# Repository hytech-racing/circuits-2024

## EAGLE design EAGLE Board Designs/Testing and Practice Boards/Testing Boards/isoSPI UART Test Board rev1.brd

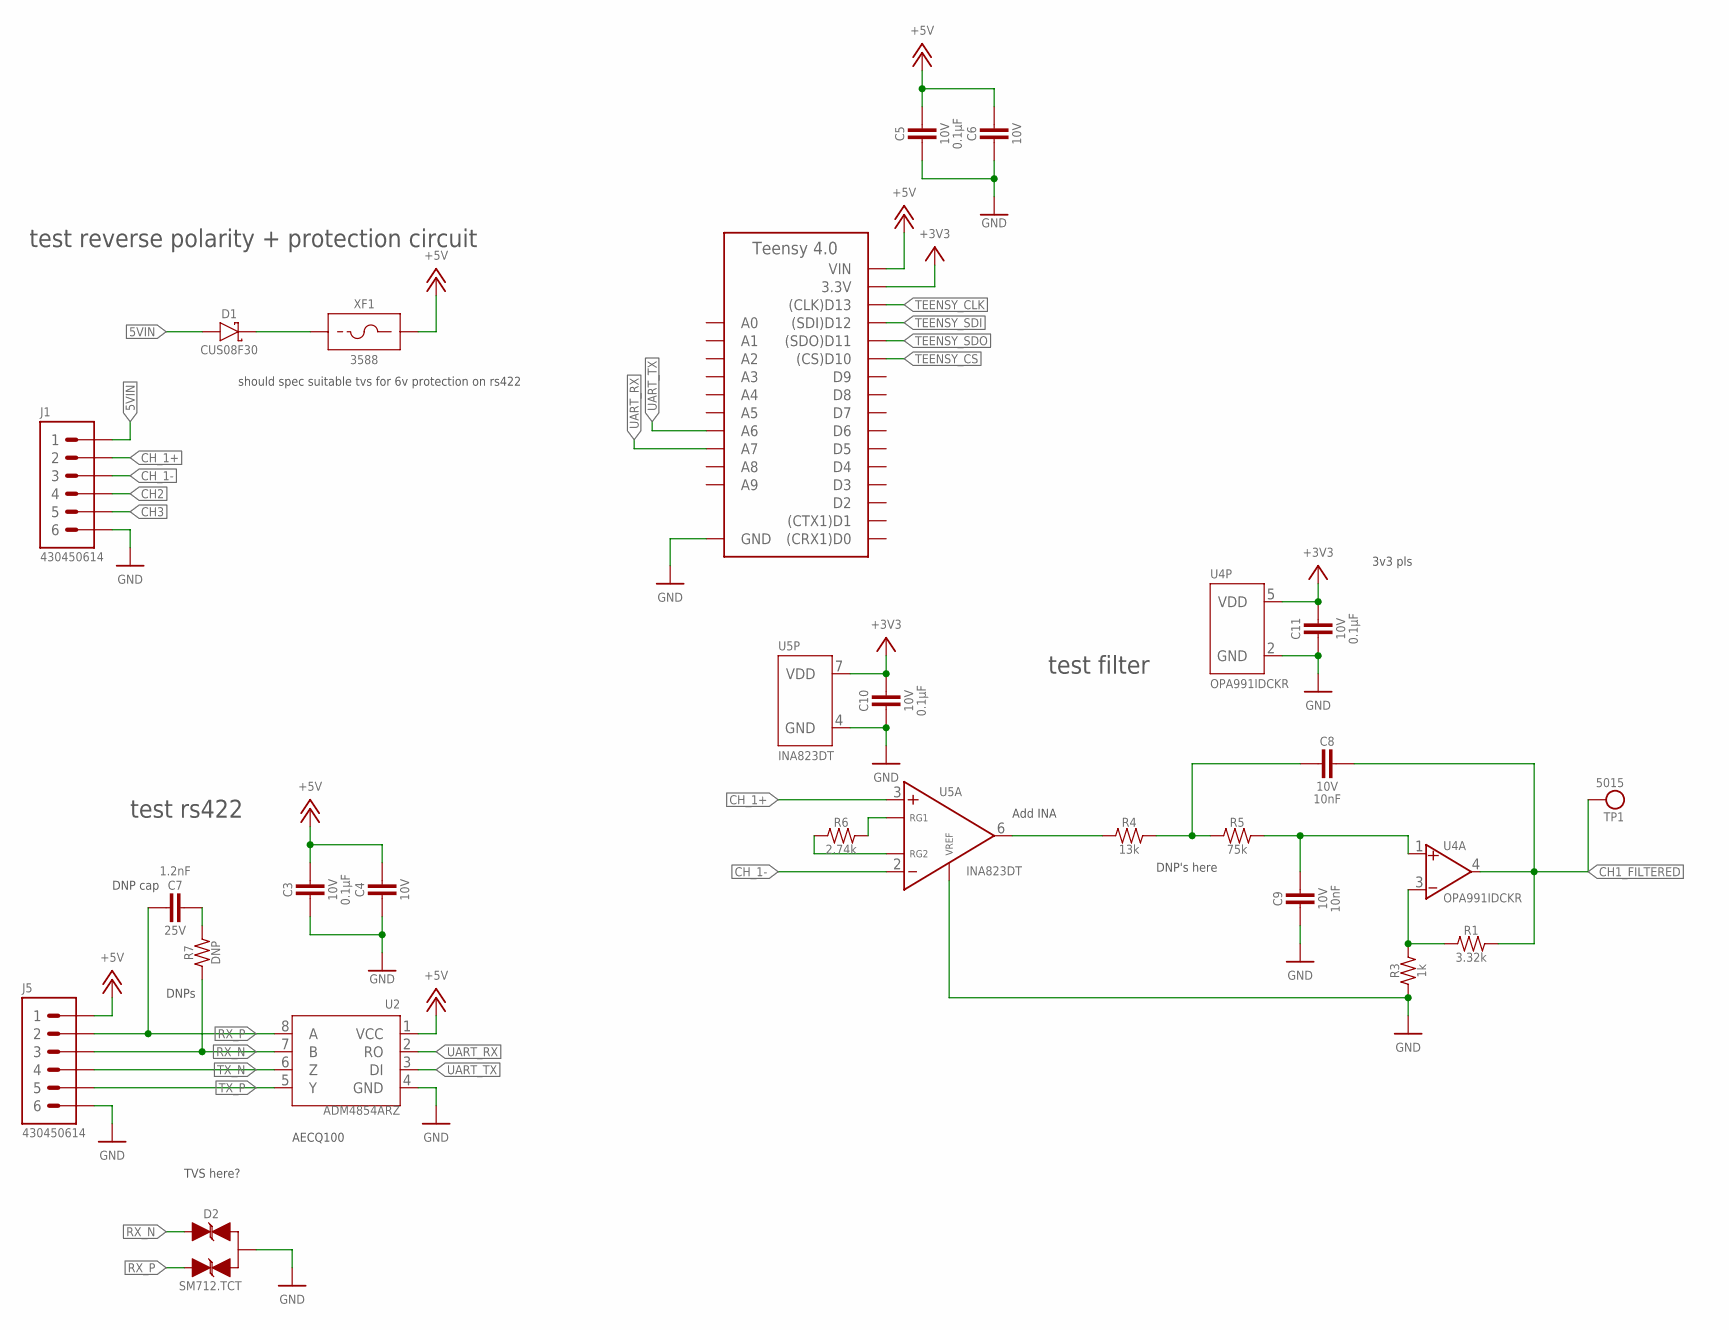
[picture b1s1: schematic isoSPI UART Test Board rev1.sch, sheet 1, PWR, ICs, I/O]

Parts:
A1: TEENSY_4.0TH; TEENSY_SHORT
C3, C5, C10, C11: CAPACITOR_0603_10V_0.1UF; 0603-CAP
C4, C6: CAPACITOR_0603_10V_1UF; 0603-CAP
C7: CAPACITOR_0603_25V_1.2NF; 0603-CAP
C8, C9: CAPACITOR_0603_10V_10NF; 0603-CAP
D1: SCHOTTKY_SOD323_30V; SOD-323
D2: TVS_BIDIRECTIONAL_DUALRS422; SOT-23
J1, J5: CONNECTOR-6_μF_T_V_BLACK; MOLEX_MICROFIT_PTH_VERTICAL_06_DUAL
R1: RESISTOR_0603_3.32K; 0603-RES
R3: RESISTOR_0603_1K; 0603-RES
R4: RESISTOR_0603_13K; 0603-RES
R5: RESISTOR_0603_75K; 0603-RES
R6: RESISTOR_0603_2.74K; 0603-RES
R7: RESISTOR_0603_DNP; 0603-RES
TP1: TEST_POINT; 5015
U2: ADM4854ARZ; SOIC-08(NARROW,0.15")
U4: OPAMP_1_CHANNEL_OPA991; SC-70-5
U5: INA823DT; SOIC-08(NARROW,0.15")
XF1: FUSE_HOLDER_MINIBLADESMD; 3588

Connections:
5VIN: D1.A, J1.1
+3V3: A1.3.3V, C10.1, C11.1, U4.5 (VDD), U5.7 (VDD); also elsewhere on the board
+5V: A1.VIN, C3.1, C4.1, C5.1, C6.1, J5.1, U2.1 (VCC), XF1.3 (2), XF1.4 (2)
CH1: R4.1, U5.6 (VOUT)
CH1_FILTERED: C8.1, R1.2, TP1.1, U4.4 (VOUT); also elsewhere on the board
CH2: J1.4; also elsewhere on the board
CH3: J1.5; also elsewhere on the board
CH_1+: J1.2, U5.3 (VIN+)
CH_1-: J1.3, U5.2 (VIN-)
GND: A1.AGND/GND (GND), A1.GND, C3.2, C4.2, C5.2, C6.2, C9.2, C10.2, C11.2, D2.3 (A), J1.6, J5.6, R3.1, U2.4 (GND), U4.2 (GND), U5.4 (GND), U5.5 (VREF); also elsewhere on the board
unnamed: C7.1, R7.2
unnamed: D1.C, XF1.1, XF1.2 (1)
unnamed: R1.1, R3.2, U4.3 (VIN-)
unnamed: R6.2, U5.1 (RG1)
unnamed: R6.1, U5.8 (RG2)
unnamed: C8.2, R4.2, R5.1
unnamed: C9.1, R5.2, U4.1 (VIN+)
RX_N: D2.1 (C1), J5.3, R7.1, U2.7 (B)
RX_P: C7.2, D2.2 (C2), J5.2, U2.8 (A)
TEENSY_CLK: A1.D13 ((CLK)D13); also elsewhere on the board
TEENSY_CS: A1.D10 ((CS)D10); also elsewhere on the board
TEENSY_SDI: A1.D12 ((SDI)D12); also elsewhere on the board
TEENSY_SDO: A1.D11 ((SDO)D11); also elsewhere on the board
TX_N: J5.4, U2.6 (Z)
TX_P: J5.5, U2.5 (Y)
UART_RX: A1.D21 (A7), U2.2 (RO)
UART_TX: A1.D20 (A6), U2.3 (DI)

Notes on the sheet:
DNP cap
test reverse polarity + protection circuit
test rs422
test filter
DNPs
should spec suitable tvs for 6v protection on rs422
TVS here?
DNP's here
Add INA
3v3 pls
AECQ100

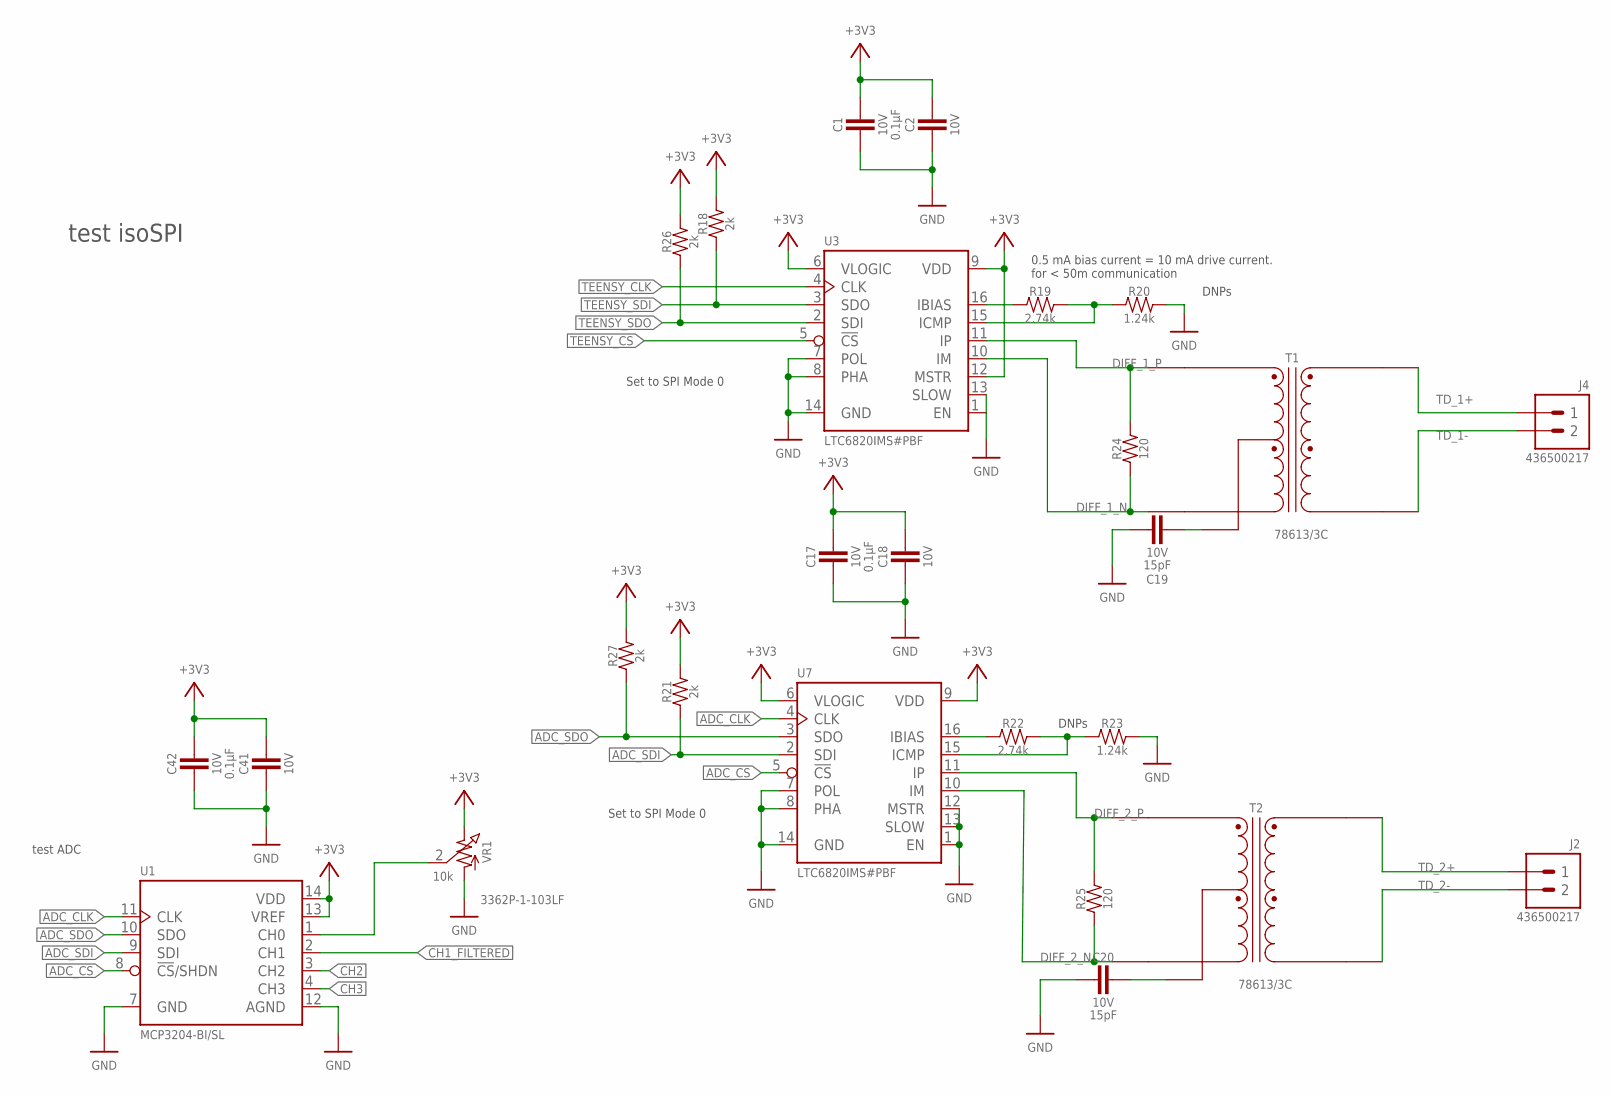
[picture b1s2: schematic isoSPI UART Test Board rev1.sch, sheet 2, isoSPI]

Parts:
C1, C17, C42: CAPACITOR_0603_10V_0.1UF; 0603-CAP
C2, C18, C41: CAPACITOR_0603_10V_1UF; 0603-CAP
C19, C20: CAPACITOR_0603_10V_15PF; 0603-CAP
J2, J4: CONNECTOR-2_MF_T_V_; MOLEX_MICROFIT_PTH_VERTICAL_02_SINGLE
R18, R21, R26, R27: RESISTOR_0603_2K; 0603-RES
R19, R22: RESISTOR_0603_2.74K; 0603-RES
R20, R23: RESISTOR_0603_1.24K; 0603-RES
R24, R25: RESISTOR_0603_120; 0603-RES
T1, T2: 78613/3C
U1: MCP3204; SOIC-14
U3, U7: LTC6820; MSOP-16
VR1: RESISTOR_TRIMPOT_10K_3362P; 3362P

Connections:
+3V3: C1.1, C2.1, C17.1, C18.1, C41.1, C42.1, R18.2, R21.2, R26.2, R27.2, U1.13 (VREF), U1.14 (VDD), U3.6 (VLOGIC), U3.9 (VDD), U3.12 (MSTR), U7.6 (VLOGIC), U7.9 (VDD), VR1.3 (2); also elsewhere on the board
ADC_CLK: U1.11 (CLK), U7.4 (CLK)
ADC_CS: U1.8 (!CS!/SHDN), U7.5 (!CS)
ADC_SDI: R21.1, U1.9 (SDI), U7.2 (SDI)
ADC_SDO: R27.1, U1.10 (SDO), U7.3 (SDO)
CH1_FILTERED: U1.2 (CH1); also elsewhere on the board
CH2: U1.3 (CH2); also elsewhere on the board
CH3: U1.4 (CH3); also elsewhere on the board
DIFF_1_N: R24.1, T1.3 (PRI_2), U3.10 (IM)
DIFF_1_P: R24.2, T1.1 (PRI_1), U3.11 (IP)
DIFF_2_N: R25.1, T2.3 (PRI_2), U7.10 (IM)
DIFF_2_P: R25.2, T2.1 (PRI_1), U7.11 (IP)
GND: C1.2, C2.2, C17.2, C18.2, C19.2, C20.2, C41.2, C42.2, R20.2, R23.2, U1.7 (GND), U1.12 (AGND), U3.1 (EN), U3.7 (POL), U3.8 (PHA), U3.13 (SLOW), U3.14 (GND), U7.1 (EN), U7.7 (POL), U7.8 (PHA), U7.12 (MSTR), U7.13 (SLOW), U7.14 (GND), VR1.1; also elsewhere on the board
unnamed: U1.1 (CH0), VR1.2 (3)
unnamed: R19.1, U3.16 (IBIAS)
unnamed: R19.2, R20.1, U3.15 (ICMP)
unnamed: R22.1, U7.16 (IBIAS)
unnamed: R22.2, R23.1, U7.15 (ICMP)
unnamed: C19.1, T1.2 (PRI_CENTER_TAP)
unnamed: C20.1, T2.2 (PRI_CENTER_TAP)
TD_1+: J4.1, T1.6 (SEC_2)
TD_1-: J4.2, T1.4 (SEC_1)
TD_2+: J2.1, T2.6 (SEC_2)
TD_2-: J2.2, T2.4 (SEC_1)
TEENSY_CLK: U3.4 (CLK); also elsewhere on the board
TEENSY_CS: U3.5 (!CS); also elsewhere on the board
TEENSY_SDI: R18.1, U3.3 (SDO); also elsewhere on the board
TEENSY_SDO: R26.1, U3.2 (SDI); also elsewhere on the board

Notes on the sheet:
0.5 mA bias current = 10 mA drive current. for < 50m communication
DNPs
test ADC
test isoSPI
Set to SPI Mode 0

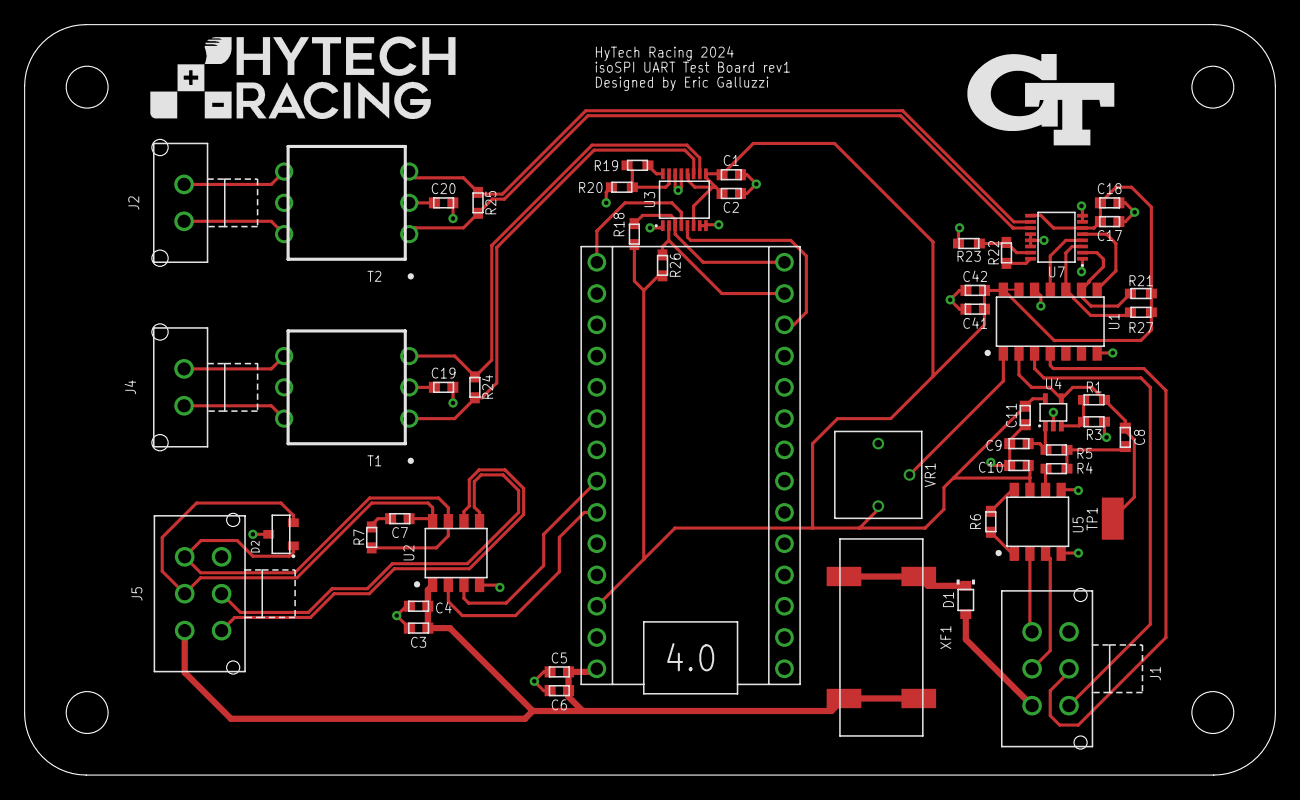
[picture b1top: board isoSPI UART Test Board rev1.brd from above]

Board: 2 copper layers, 101.6 x 61.0 mm, 57 parts (1 on the bottom side), 46 nets.

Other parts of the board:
U$1, U$2, U$3, U$4: MOUNTING_M3
U$5: LOGO_HYTECH_MEDIUM
U$6: LOGO_GT_MEDIUM

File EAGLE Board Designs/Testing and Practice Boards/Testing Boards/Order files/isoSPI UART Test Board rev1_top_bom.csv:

Comment,Designator,Footprint,LCSC Part #
ADM4854ARZ,U2,SOIC-08(NARROW 0.15"),
CAPACITOR_0603_10V_0.1UF,C1 C3 C5 C10 C11 C17 C42,0603-CAP,
CAPACITOR_0603_10V_1UF,C2 C4 C6 C18 C41,0603-CAP,
CAPACITOR_0603_10V_10NF,C8 C9,0603-CAP,
CAPACITOR_0603_10V_15PF,C19 C20,0603-CAP,
CAPACITOR_0603_25V_1.2NF,C7,0603-CAP,
FUSE_HOLDER_MINIBLADESMD,XF1,3588,
INA823DT,U5,SOIC-08(NARROW 0.15"),
LTC6820,U3 U7,MSOP-16,
MCP3204,U1,SOIC-14,
OPAMP_1_CHANNEL_OPA991,U4,SC-70-5,
RESISTOR_0603_1.24K,R20 R23,0603-RES,
RESISTOR_0603_1K,R3,0603-RES,
RESISTOR_0603_2.74K,R6 R19 R22,0603-RES,
RESISTOR_0603_2K,R18 R21 R26 R27,0603-RES,
RESISTOR_0603_3.32K,R1,0603-RES,
RESISTOR_0603_13K,R4,0603-RES,
RESISTOR_0603_75K,R5,0603-RES,
RESISTOR_0603_120,R24 R25,0603-RES,
RESISTOR_0603_DNP,R7,0603-RES,
RESISTOR_1206_HV46.4K,R2,1206-RES,
SCHOTTKY_SOD323_30V,D1,SOD-323,
TEST_POINT,TP1,5015,
TVS_BIDIRECTIONAL_DUALRS422,D2,SOT-23,

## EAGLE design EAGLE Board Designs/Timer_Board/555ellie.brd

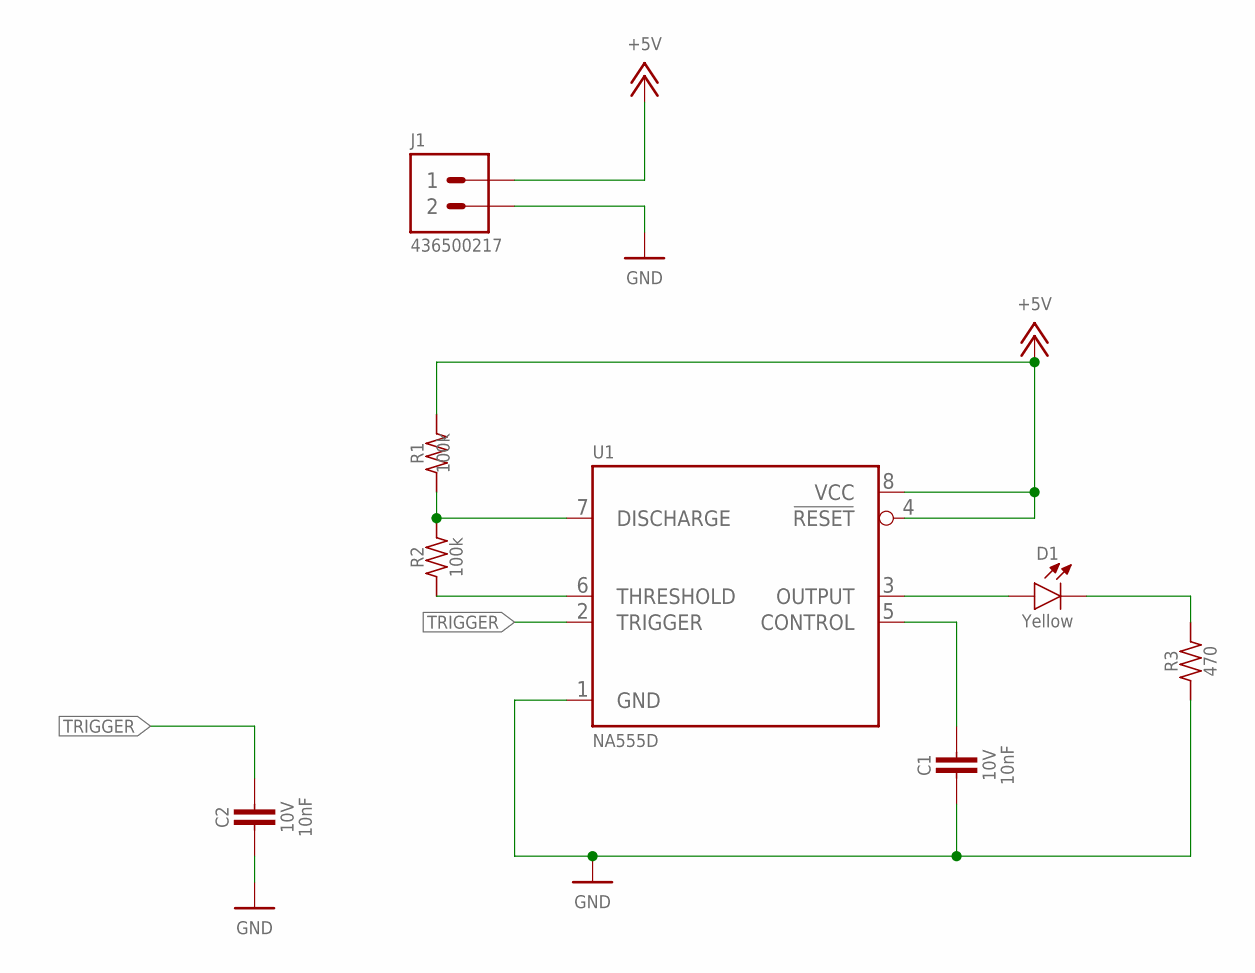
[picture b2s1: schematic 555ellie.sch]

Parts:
C1, C2: CAPACITOR_0603_10V_10NF; 0603-CAP
D1: LED_0603_YELLOW; 0603-LED
J1: CONNECTOR-2_μF_T_V_BLACK; MOLEX_MICROFIT_PTH_VERTICAL_02_DUAL
R1, R2: RESISTOR_0603_100K; 0603-RES
R3: RESISTOR_0603_470; 0603-RES
U1: NA555; SOIC-08(NARROW,0.15")

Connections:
+5V: J1.1, R1.2, U1.4 (!RESET), U1.8 (VCC)
GND: C2.2, J1.2
unnamed: R2.1, U1.6 (THRESHOLD)
unnamed: R1.1, R2.2, U1.7 (DISCHARGE)
unnamed: D1.2 (A), U1.3 (OUTPUT)
unnamed: D1.1 (C), R3.2
unnamed: C1.2, R3.1, U1.1 (GND)
unnamed: C1.1, U1.5 (CONTROL)
TRIGGER: C2.1, U1.2 (TRIGGER)

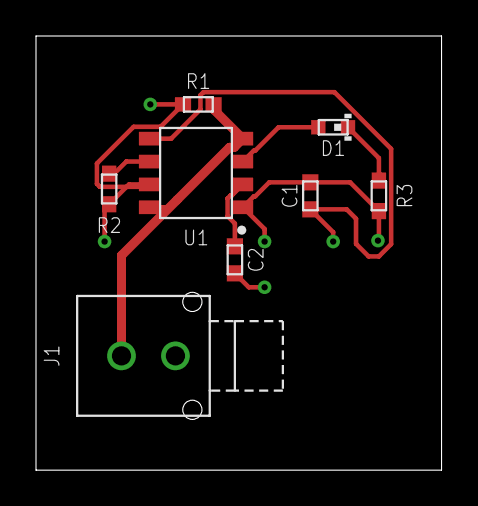
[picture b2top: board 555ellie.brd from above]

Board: 2 copper layers, 22.5 x 24.1 mm, 8 parts (0 on the bottom side), 9 nets.

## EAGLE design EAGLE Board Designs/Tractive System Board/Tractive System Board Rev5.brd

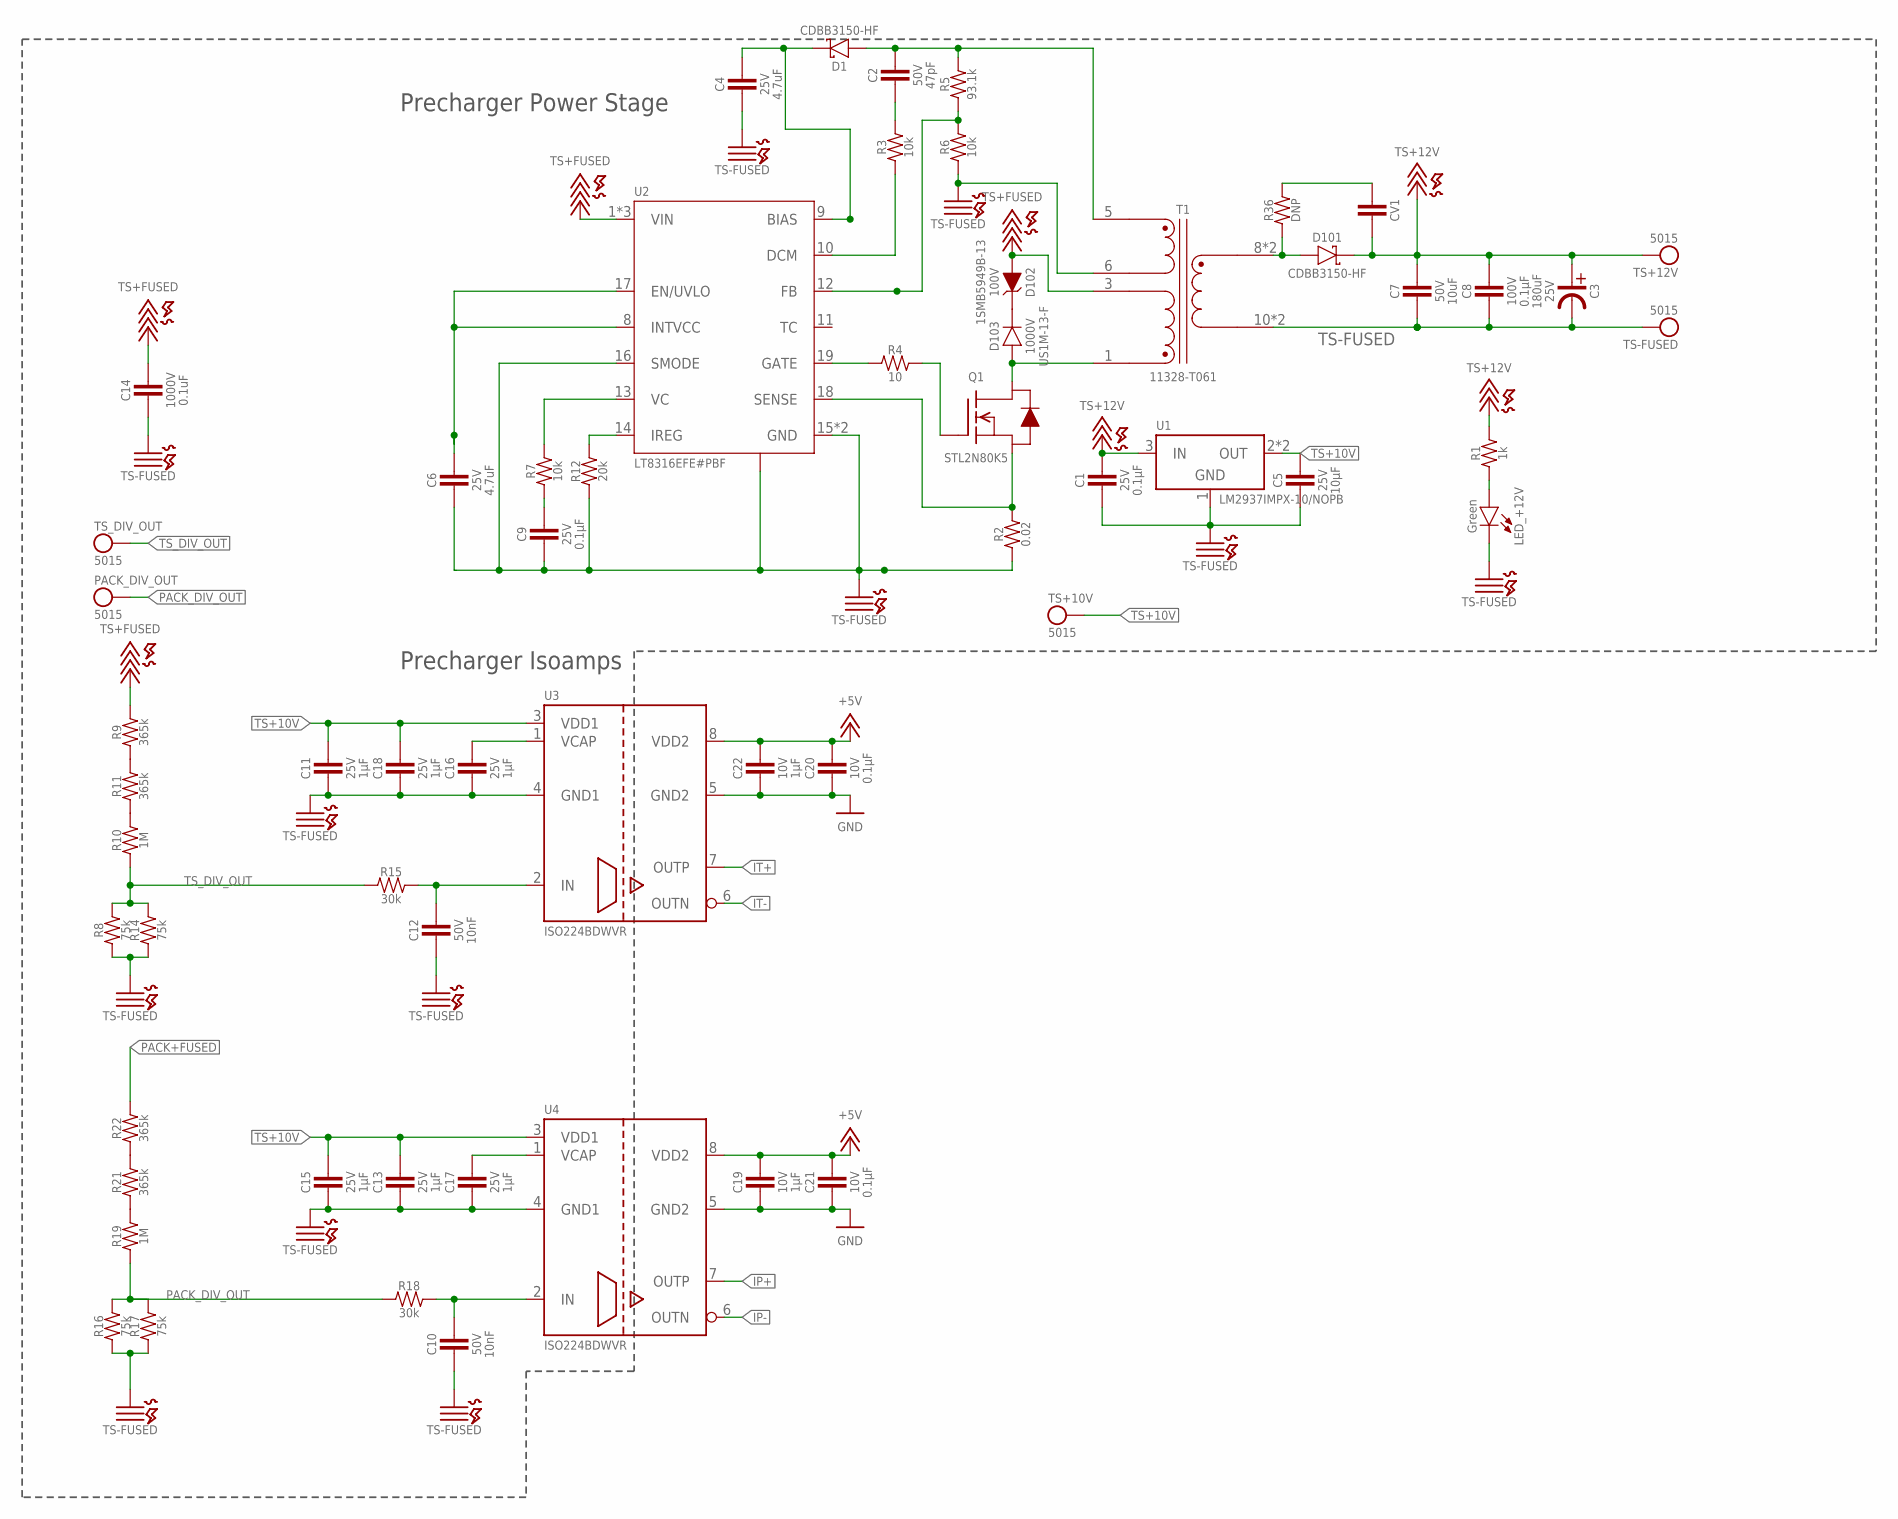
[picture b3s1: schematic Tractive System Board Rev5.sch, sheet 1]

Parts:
C1, C9: CAPACITOR_0603_25V_0.1UF; 0603-CAP
C2: CAPACITOR_0603_50V_47PF; 0603-CAP
C3: CAPACITOR_ELECTROLYTIC_A759_180UF; A759
C4, C6: CAPACITOR_0603_25V_4.7UF; 0603-CAP
C5: CAPACITOR_0603_25V_10UF; 0603-CAP
C7: CAPACITOR_0805_50V_10UF; 0805-CAP
C8: CAPACITOR_0603_100V_0.1UF; 0603-CAP
C10, C12: CAPACITOR_0603_50V_10NF; 0603-CAP
C11, C13, C15, C16, C17, C18: CAPACITOR_0603_25V_1UF; 0603-CAP
C14: CAPACITOR_1812_1000V_0.1UF; 1812-CAP
C19, C22: CAPACITOR_0603_10V_1UF; 0603-CAP
C20, C21: CAPACITOR_0603_10V_0.1UF; 0603-CAP
CV1: CAPACITOR_VALUE; 0603-CAP
D1, D101: SCHOTTKY_DO-214AA_150V; DO-214AA
D102: ZENER_DO-214AA_100V; DO-214AA
D103: RECTIFIER_1000V_SMA; SMA
LED_+12V: LED_0603_GREEN; 0603-LED
PACK_DIV_OUT: TEST_POINT; 5015
Q1: TRANSISTOR_N_MOS_POWERFLAT5X6_STL2N80K5; POWERFLAT5X6
R1: RESISTOR_0603_1K; 0603-RES
R2: RESISTOR_0603_0.02; 0603-RES
R3, R6, R7: RESISTOR_0603_10K; 0603-RES
R4: RESISTOR_0603_10; 0603-RES
R5: RESISTOR_0603_93.1K; 0603-RES
R8, R14, R16, R17: RESISTOR_0805_HV75K; 0805-RES
R9, R11, R21, R22: RESISTOR_0805_HV365K; 0805-RES
R10, R19: RESISTOR_0805_HV1M; 0805-RES
R12: RESISTOR_0603_20K; 0603-RES
R15, R18: RESISTOR_0603_; 0603-RES
R36: RESISTOR_0603_DNP; 0603-RES
T1: TRANSFORMER(3W); PQ2620
TS+10V, TS+12V: TEST_POINT; 5015
TS-FUSED: TEST_POINT; 5015
TS_DIV_OUT: TEST_POINT; 5015
U1: VOLTAGE_REGULATOR_SOT-223_10V; SOT-223
U2: LT8316; TSSOP-20(16)
U3, U4: ISO224B_AIRGAP; SOIC-08(WIDE,0.295")-AIRGAP

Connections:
+5V: C19.1, C20.1, C21.1, C22.1, U3.8 (VDD2), U4.8 (VDD2); also elsewhere on the board
GND: C19.2, C20.2, C21.2, C22.2, U3.5 (GND2), U4.5 (GND2); also elsewhere on the board
IP+: U4.7 (OUTP); also elsewhere on the board
IP-: U4.6 (OUTN); also elsewhere on the board
IT+: U3.7 (OUTP); also elsewhere on the board
IT-: U3.6 (OUTN); also elsewhere on the board
unnamed: R21.2, R22.1
unnamed: R9.1, R11.2
unnamed: D102.2 (C), D103.C
unnamed: R10.2, R11.1
unnamed: R19.2, R21.1
unnamed: D103.A, Q1.D, T1.1
unnamed: C4.1, D1.2 (C), U2.9 (BIAS)
unnamed: R5.1, R6.2, U2.12 (FB)
unnamed: C2.2, R3.2
unnamed: R3.1, U2.10 (DCM)
unnamed: R7.2, U2.13 (VC)
unnamed: R12.2, U2.14 (IREG)
unnamed: C2.1, D1.1 (A), R5.2, T1.5
unnamed: C9.1, R7.1
unnamed: C6.1, U2.8 (INTVCC), U2.17 (EN/UVLO)
unnamed: R4.1, U2.19 (GATE)
unnamed: D101.1 (A), R36.1, T1.8 (8,9), T1.9 (8,9)
unnamed: LED_+12V.2 (A), R1.1
unnamed: Q1.S, R2.2, U2.18 (SENSE)
unnamed: Q1.G, R4.2
unnamed: CV1.2, R36.2
unnamed: C10.1, R18.2, U4.2 (IN)
unnamed: C12.1, R15.2, U3.2 (IN)
unnamed: C17.1, U4.1 (VCAP)
unnamed: C16.1, U3.1 (VCAP)
PACK+FUSED: R22.2; also elsewhere on the board
PACK_DIV_OUT: PACK_DIV_OUT.1, R16.2, R17.2, R18.1, R19.1
TS+10V: C5.1, C11.1, C13.1, C15.1, C18.1, TS+10V.1, U1.2 (OUT), U1.4 (OUT), U3.3 (VDD1), U4.3 (VDD1)
TS+12V: C1.1, C3.PLUS, C7.1, C8.1, CV1.1, D101.2 (C), R1.2, TS+12V.1, U1.3 (IN); also elsewhere on the board
TS+FUSED: C14.1, D102.1 (A), R9.2, T1.3, U2.1 (VIN), U2.2 (VIN), U2.3 (VIN); also elsewhere on the board
TS-FUSED: C1.2, C3.MINUS, C4.2, C5.2, C6.2, C7.2, C8.2, C9.2, C10.2, C11.2, C12.2, C13.2, C14.2, C15.2, C16.2, C17.2, C18.2, LED_+12V.1 (C), R2.1, R6.1, R8.1, R12.1, R14.1, R16.1, R17.1, T1.6, T1.10 (10,11), T1.11 (10,11), TS-FUSED.1, U1.1 (GND), U2.15 (GND), U2.16 (SMODE), U2.20 (GND), U2.THERMAL, U3.4 (GND1), U4.4 (GND1); also elsewhere on the board
TS_DIV_OUT: R8.2, R10.1, R14.2, R15.1, TS_DIV_OUT.1

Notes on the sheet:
Precharger Power Stage
Precharger Isoamps

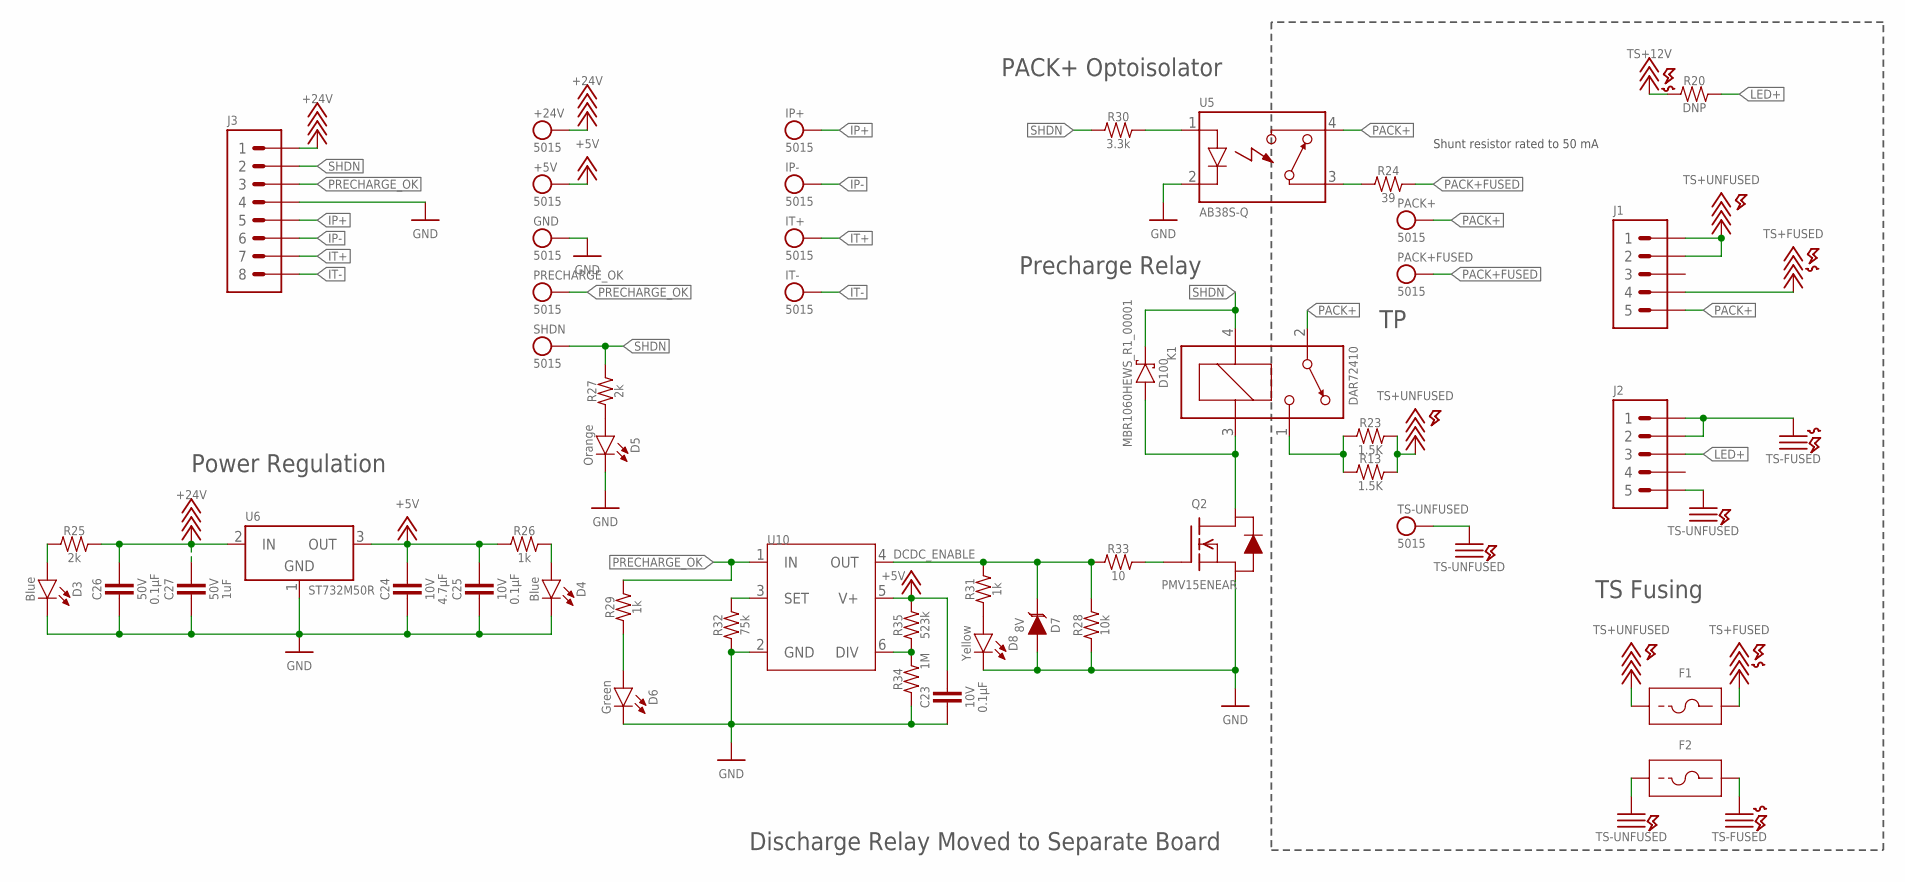
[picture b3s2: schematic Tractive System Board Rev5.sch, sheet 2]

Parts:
+5V, +24V: TEST_POINT; 5015
C23, C25: CAPACITOR_0603_10V_0.1UF; 0603-CAP
C24: CAPACITOR_0603_10V_4.7UF; 0603-CAP
C26: CAPACITOR_0603_50V_0.1UF; 0603-CAP
C27: CAPACITOR_0603_50V_1UF; 0603-CAP
D3, D4: LED_0603_BLUE; 0603-LED
D5: LED_0603_ORANGE; 0603-LED
D6: LED_0603_GREEN; 0603-LED
D7: TVS__8V; SOT-23
D8: LED_0603_YELLOW; 0603-LED
D100: SCHOTTKY_SOD323_60V; SOD-323
F1, F2: FUSE_HOLDER_122; 122
GND: TEST_POINT; 5015
IP+: TEST_POINT; 5015
IP-: TEST_POINT; 5015
IT+: TEST_POINT; 5015
IT-: TEST_POINT; 5015
J1: CONNECTOR-5_MICRO_V7S_; MOLEX_MICROFIT_PTH_VERTICAL_07_SINGLE_SPACED
J2: CONNECTOR-5_MICRO_V6S_; MOLEX_MICROFIT_PTH_VERTICAL_06_SINGLE_SPACED
J3: CONNECTOR-8_μF_T_V_BLACK; MOLEX_MICROFIT_PTH_VERTICAL_08_DUAL
K1: RELAY_SPST_NO_D_24; D
PACK+: TEST_POINT; 5015
PACK+FUSED: TEST_POINT; 5015
PRECHARGE_OK: TEST_POINT; 5015
Q2: TRANSISTOR_N_MOS__PMV15ENEA; SOT-23
R13, R23: RESISTOR_B20-SHORTENED_1.5K; B20-SHORTENED
R20: RESISTOR_0603_DNP; 0603-RES
R24: RESISTOR_0603_39; 0603-RES
R25, R27: RESISTOR_0603_2K; 0603-RES
R26, R29, R31: RESISTOR_0603_1K; 0603-RES
R28: RESISTOR_0603_10K; 0603-RES
R30: RESISTOR_0603_3.3K; 0603-RES
R32: RESISTOR_0603_75K; 0603-RES
R33: RESISTOR_0603_10; 0603-RES
R34: RESISTOR_0805_1M; 0805-RES
R35: RESISTOR_0805_523K; 0805-RES
SHDN: TEST_POINT; 5015
TS-UNFUSED: TEST_POINT; 5015
U5: RELAY_SOLIDSTATE_NO_AB38S-Q-AIRGAP; SOP-04-AIRGAP
U6: VOLTAGE_REGULATOR_SOT-23-5_5V; SOT-23-5
U10: LTC6994-2; SOT-23-6

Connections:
+5V: +5V.1, C23.1, C24.1, C25.1, R26.1, R35.2, U6.3 (OUT), U10.5 (V+); also elsewhere on the board
+24V: +24V.1, C26.1, C27.1, J3.1, R25.2, U6.2 (IN)
DCDC_ENABLE: D7.3 (C), R28.2, R31.2, R33.1, U10.4 (OUT)
GND: C23.2, C24.2, C25.2, C26.2, C27.2, D3.1 (C), D4.1 (C), D5.1 (C), D6.1 (C), D7.1 (A), D8.1 (C), GND.1, J3.4, Q2.2 (S), R28.1, R32.1, R34.1, U5.2 (CONTROL-), U6.1 (GND), U10.2 (GND); also elsewhere on the board
IP+: IP+.1, J3.5; also elsewhere on the board
IP-: IP-.1, J3.6; also elsewhere on the board
IT+: IT+.1, J3.7; also elsewhere on the board
IT-: IT-.1, J3.8; also elsewhere on the board
LED+: J2.3, R20.2
unnamed: D5.2 (A), R27.1
unnamed: Q2.1 (G), R33.2
unnamed: R32.2, U10.3 (SET)
unnamed: R34.2, R35.1, U10.6 (DIV)
unnamed: D6.2 (A), R29.1
unnamed: D8.2 (A), R31.1
unnamed: D3.2 (A), R25.1
unnamed: D4.2 (A), R26.2
unnamed: D100.A, K1.3 (COIL-), Q2.3 (D)
unnamed: K1.1 (CONTACT2), R13.1, R23.1
unnamed: R30.2, U5.1 (CONTROL+)
unnamed: R24.1, U5.3 (CONTACT1)
PACK+: J1.5, K1.2 (CONTACT1), PACK+.1, U5.4 (CONTACT2)
PACK+FUSED: PACK+FUSED.1, R24.2; also elsewhere on the board
PRECHARGE_OK: J3.3, PRECHARGE_OK.1, R29.2, U10.1 (IN)
SHDN: D100.C, J3.2, K1.4 (COIL+), R27.2, R30.1, SHDN.1
TS+12V: R20.1; also elsewhere on the board
TS+FUSED: F1.3 (2), F1.4 (2), J1.4; also elsewhere on the board
TS+UNFUSED: F1.1, F1.2 (1), J1.1, J1.2, R13.2, R23.2
TS-FUSED: F2.3 (2), F2.4 (2), J2.1, J2.2; also elsewhere on the board
TS-UNFUSED: F2.1, F2.2 (1), J2.5, TS-UNFUSED.1

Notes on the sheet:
PACK+ Optoisolator
Precharge Relay
Discharge Relay Moved to Separate Board
TS Fusing
Power Regulation
Shunt resistor rated to 50 mA

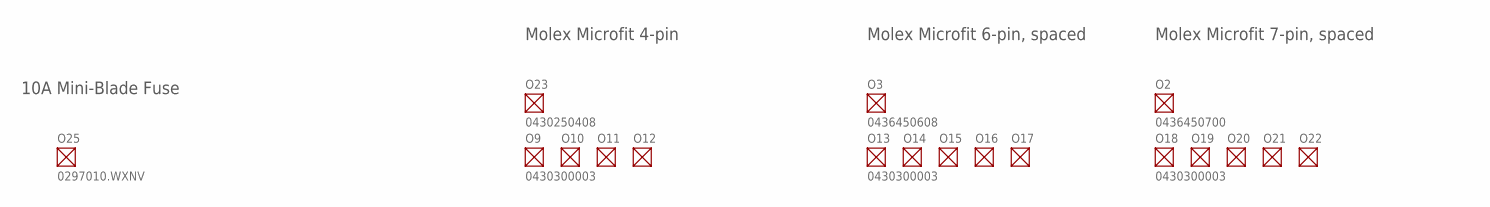
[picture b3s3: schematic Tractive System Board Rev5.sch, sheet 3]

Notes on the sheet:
10A Mini-Blade Fuse
Molex Microfit 4-pin
Molex Microfit 6-pin, spaced
Molex Microfit 7-pin, spaced

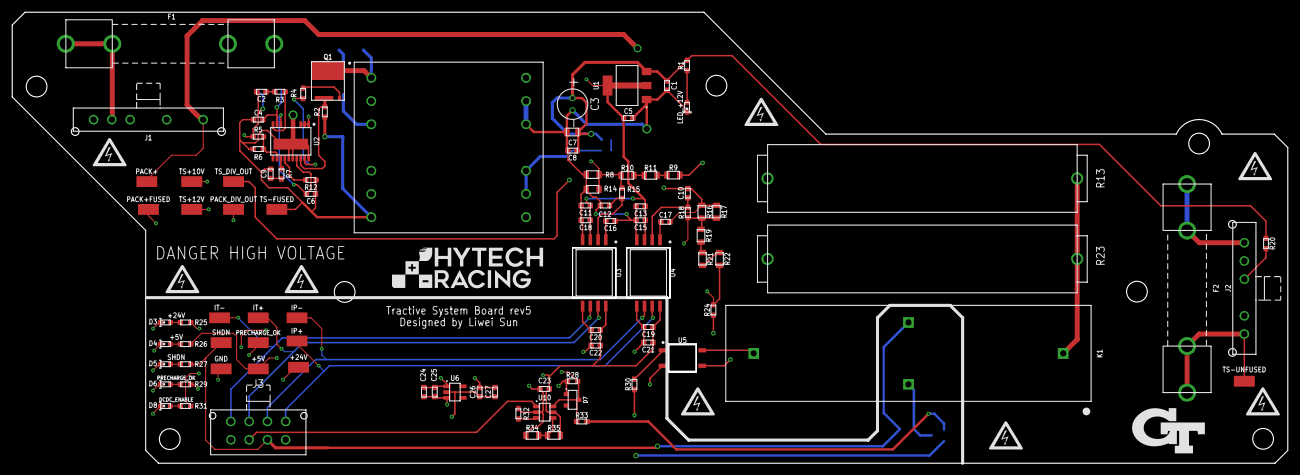
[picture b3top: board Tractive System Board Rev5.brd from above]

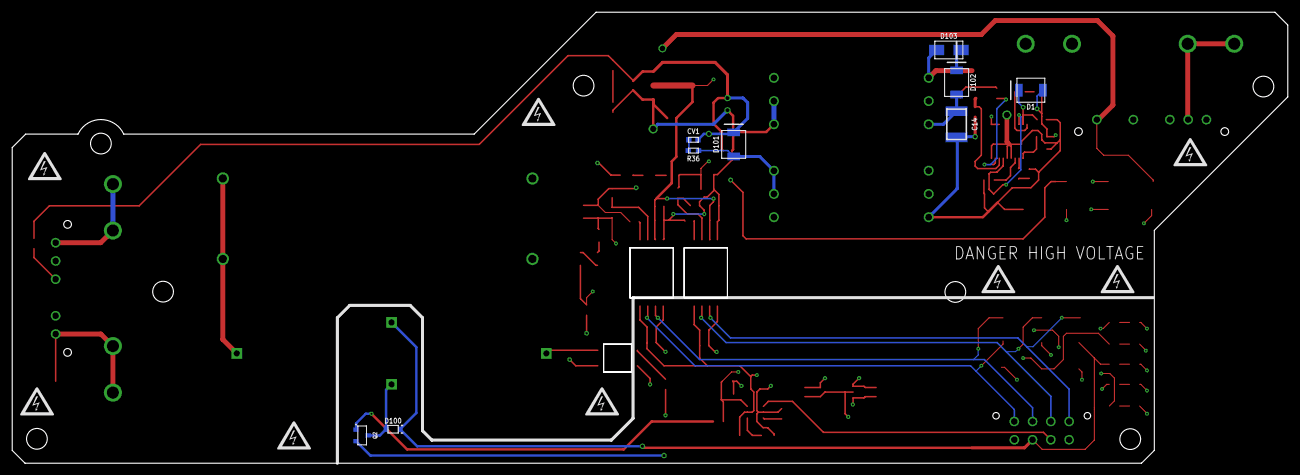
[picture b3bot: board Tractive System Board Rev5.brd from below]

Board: 4 copper layers, 209.3 x 74.0 mm, 135 parts (17 on the bottom side), 58 nets.

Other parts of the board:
$$U$1, $$U$4, $$U$6, $$U$8, $$U$104, $$U$105, $$U$106, $$U$107: HV_MEDIUM
$$U$2, $$U$3, $$U$5: MOUNTING_M3
U$7: DANGER_HIGH_VOLTAGE
U$9, U$13, U$14, U$15, U$100, U$101, U$102, U$103: HV_MEDIUM
U$10: LOGO_HYTECH_MEDIUM
U$11, U$12, U$16, U$17: MOUNTING_M3
U$18: LOGO_GT_MEDIUM

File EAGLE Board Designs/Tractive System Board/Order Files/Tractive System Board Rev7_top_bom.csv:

Comment,Designator,Footprint,LCSC Part #
CAPACITOR_0603_10V_0.1UF,C20 C21 C23 C25,0603-CAP,
CAPACITOR_0603_10V_1UF,C19 C22,0603-CAP,
CAPACITOR_0603_25V_0.1UF,C1 C9,0603-CAP,
CAPACITOR_0603_25V_1UF,C11 C13 C15 C16 C17 C18,0603-CAP,
CAPACITOR_0603_25V_4.7UF,C4 C6,0603-CAP,
CAPACITOR_0603_25V_10UF,C5 C24,0603-CAP,
CAPACITOR_0603_50V_0.1UF,C26,0603-CAP,
CAPACITOR_0603_50V_1UF,C27,0603-CAP,
CAPACITOR_0603_50V_10NF,C10 C12,0603-CAP,
CAPACITOR_0603_50V_47PF,C2,0603-CAP,
CAPACITOR_0603_100V_0.1UF,C8,0603-CAP,
CAPACITOR_0805_50V_10UF,C7,0805-CAP,
CAPACITOR_1206_630V_10NF,C3,1206-CAP,
ISO224B_AIRGAP,U3,SOIC-08(WIDE 0.295")-AIRGAP,
ISO224B_AIRGAP,U4,SOIC-08(WIDE 0.295")-AIRGAP,
LED_0603_BLUE,D3 D4,0603-LED,
LED_0603_GREEN,D6 LED_+12V,0603-LED,
LED_0603_ORANGE,D5,0603-LED,
LED_0603_YELLOW,D8,0603-LED,
LT8316,U2,TSSOP-20(16),
LTC6994-2,U10,SOT-23-6,
RECTIFIER_800V_SOD-123FA,D2,SOD-123FA,
RELAY_SOLIDSTATE_NO_AB38S-Q-AIRGAP,U5,SOP-04-AIRGAP,
RESISTOR_0603_,R15 R18,0603-RES,
RESISTOR_0603_0.02,R2,0603-RES,
RESISTOR_0603_1K,R1 R26 R29 R31,0603-RES,
RESISTOR_0603_2K,R25 R27,0603-RES,
RESISTOR_0603_3.3K,R30,0603-RES,
RESISTOR_0603_10,R4 R33,0603-RES,
RESISTOR_0603_10K,R3 R6 R7 R28,0603-RES,
RESISTOR_0603_20K,R12,0603-RES,
RESISTOR_0603_39,R24,0603-RES,
RESISTOR_0603_75K,R32,0603-RES,
RESISTOR_0603_93.1K,R5,0603-RES,
RESISTOR_0603_DNP,R20,0603-RES,
RESISTOR_0805_1M,R34,0805-RES,
RESISTOR_0805_523K,R35,0805-RES,
RESISTOR_0805_HV1M,R10 R19,0805-RES,
RESISTOR_0805_HV75K,R8 R14 R16 R17,0805-RES,
RESISTOR_0805_HV330K,R39,0805-RES,
RESISTOR_0805_HV365K,R9 R11 R21 R22 R37 R38,0805-RES,
RESISTOR_1206_HV46.4K,R40 R41,1206-RES,
TEST_POINT,+5V +24V EN/UVLO GND IP+ IP- IT+ IT- PACK+ PACK+FUSED PACK_DIV_OUT PRECHARGE_OK SHDN TS+10V TS+12V TS-FUSED TS-UNFUSED TS_DIV_OUT,5015,
TRANSISTOR_N_MOS_POWERFLAT5X6_STL2N80K5,Q1,POWERFLAT5X6,
TVS__8V,D7,SOT-23,
VOLTAGE_REGULATOR_SOT-223_10V,U1,SOT-223,
